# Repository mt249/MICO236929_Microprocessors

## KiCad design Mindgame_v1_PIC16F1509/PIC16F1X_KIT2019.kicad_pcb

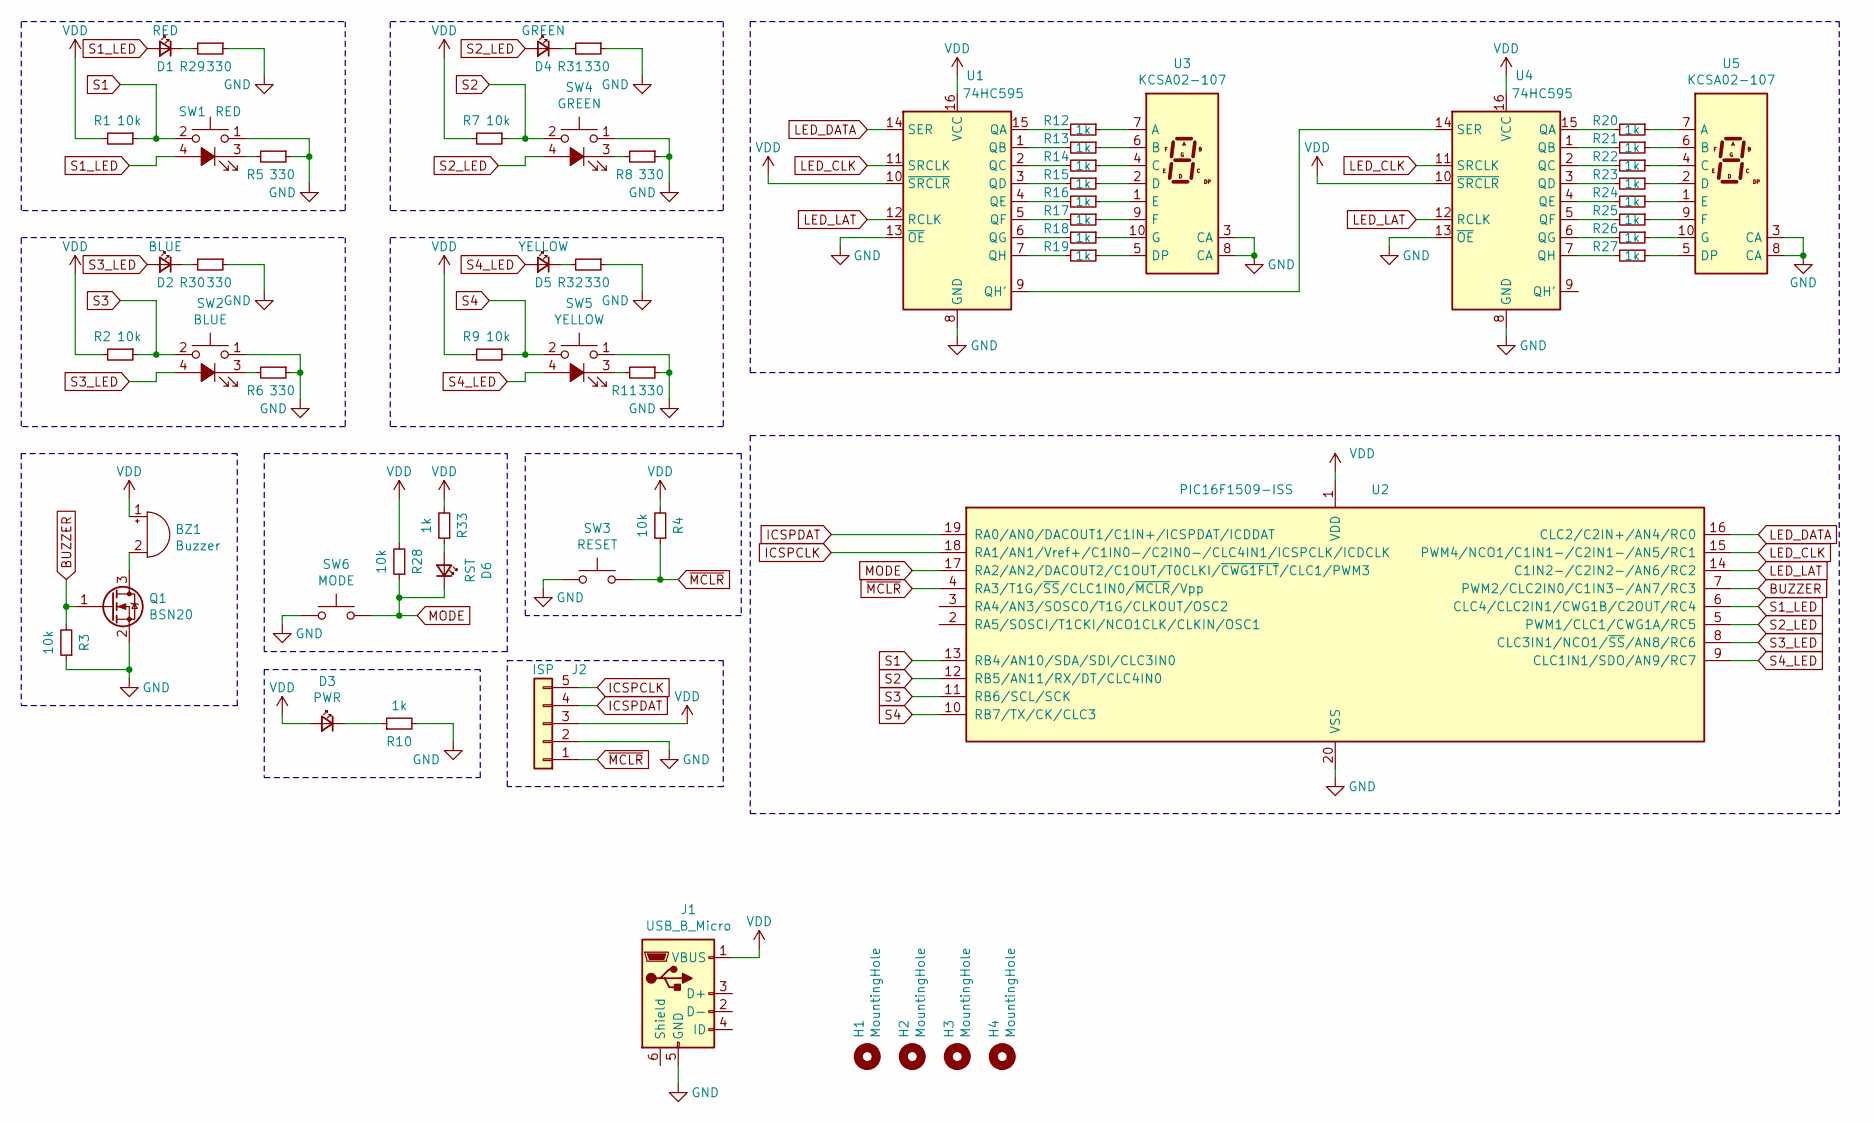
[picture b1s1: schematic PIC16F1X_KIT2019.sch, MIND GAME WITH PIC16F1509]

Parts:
BZ1: Buzzer; Buzzer_12x9.5RM7.6
D1: RED; LED_D8.0mm
D2: BLUE; LED_D8.0mm
D3: PWR; LED_0805_2012Metric_Pad1.15x1.40mm_HandSolder
D4: GREEN; LED_D8.0mm
D5: YELLOW; LED_D8.0mm
D6: RST; LED_0805_2012Metric_Pad1.15x1.40mm_HandSolder
H1, H2, H3, H4: MountingHole; MountingHole_2.7mm_M2.5_ISO7380_Pad
J1: USB_B_Micro; USB_Micro-B_GCT_USB3076-30-A
J2: ISP; PinHeader_1x05_P2.54mm_Horizontal
Q1: BSN20; SOT-23
R1, R2, R3, R4, R7, R9, R28: 10k; R_0603_1608Metric_Pad1.05x0.95mm_HandSolder
R5, R6, R8, R11, R29, R30, R31, R32: 330; R_0805_2012Metric_Pad1.15x1.40mm_HandSolder
R10, R12, R13, R14, R15, R16, R17, R18, R19, R20, R21, R22, R23, R24, R25, R26, R27, R33: 1k; R_0603_1608Metric_Pad1.05x0.95mm_HandSolder
SW1: RED; SW_PUSH-12mm
SW2: BLUE; SW_PUSH-12mm
SW3: RESET; SW_SPST_CK_RS282G05A3
SW4: GREEN; SW_PUSH-12mm
SW5: YELLOW; SW_PUSH-12mm
SW6: MODE; SW_SPST_CK_RS282G05A3
U1, U4: 74HC595; SOIC-16_3.9x9.9mm_P1.27mm
U2: PIC16F1509-ISS; SSOP-20_5.3x7.2mm_P0.65mm
U3, U5: KCSA02-107; 7SegmentLED_LTS6760_LTS6780

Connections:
BUZZER: Q1.1 (G), R3.2, U2.7 (PWM2/CLC2IN0/C1IN3-/AN7/RC3)
GND: J1.5 (GND), J2.2, Q1.2 (S), R3.1, R5.1, R6.1, R8.1, R10.2, R11.1, R29.1, R30.1, R31.1, R32.1, SW1.1, SW2.1, SW3.1, SW4.1, SW5.1, SW6.1, U1.8 (GND), U1.13 (~OE), U2.20 (VSS), U3.3 (CA), U3.8 (CA), U4.8 (GND), U4.13 (~OE), U5.3 (CA), U5.8 (CA); also elsewhere on the board
Hint: D6.1 (K), R28.1, SW6.2, U2.17 (RA2/AN2/DACOUT2/C1OUT/T0CLKI/~CWG1FLT~/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)
ICSPCLK: J2.5, U2.18 (RA1/AN1/Vref+/C1IN0-/C2IN0-/CLC4IN1/ICS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)
ICSPDAT: J2.4, U2.19 (RA0/AN0/DACOUT1/C1IN+/ICSPDAT/ICDDAT)
LED_CLK: U1.11 (SRCLK), U2.15 (PWM4/NCO1/C1IN1-/C2IN1-/AN5/RC1), U4.11 (SRCLK)
LED_DATA: U1.14 (SER), U2.16 (CLC2/C2IN+/AN4/RC0)
LED_LAT: U1.12 (RCLK), U2.14 (C1IN2-/C2IN2-/AN6/RC2), U4.12 (RCLK)
unnamed: BZ1.2 (+), Q1.3 (D)
unnamed 9: D1.1 (K), R29.2; also elsewhere on the board
unnamed 10: D2.1 (K), R30.2; also elsewhere on the board
unnamed: D3.1 (K), R10.1
unnamed 12: D4.1 (K), R31.2; also elsewhere on the board
unnamed 13: D5.1 (K), R32.2; also elsewhere on the board
unnamed: D6.2 (A), R33.1
unnamed: R5.2, SW1.3 (K)
unnamed: R6.2, SW2.3 (K)
unnamed: R8.2, SW4.3 (K)
unnamed: R11.2, SW5.3 (K)
unnamed: R12.1, U3.7 (A)
unnamed: R12.2, U1.15 (QA)
unnamed: R13.1, U3.6 (B)
unnamed: R13.2, U1.1 (QB)
unnamed: R14.1, U3.4 (C)
unnamed: R14.2, U1.2 (QC)
unnamed: R15.1, U3.2 (D)
unnamed: R15.2, U1.3 (QD)
unnamed: R16.1, U3.1 (E)
unnamed: R16.2, U1.4 (QE)
unnamed: R17.1, U3.9 (F)
unnamed: R17.2, U1.5 (QF)
unnamed: R18.1, U3.10 (G)
unnamed: R18.2, U1.6 (QG)
unnamed: R19.1, U3.5 (DP)
unnamed: R19.2, U1.7 (QH)
unnamed: R20.1, U5.7 (A)
unnamed: R20.2, U4.15 (QA)
unnamed: R21.1, U5.6 (B)
unnamed: R21.2, U4.1 (QB)
unnamed: R22.1, U5.4 (C)
unnamed: R22.2, U4.2 (QC)
unnamed: R23.1, U5.2 (D)
unnamed: R23.2, U4.3 (QD)
unnamed: R24.1, U5.1 (E)
unnamed: R24.2, U4.4 (QE)
unnamed: R25.1, U5.9 (F)
unnamed: R25.2, U4.5 (QF)
unnamed: R26.1, U5.10 (G)
unnamed: R26.2, U4.6 (QG)
unnamed: R27.1, U5.5 (DP)
unnamed: R27.2, U4.7 (QH)
unnamed: U1.9 (QH'), U4.14 (SER)
S1: R1.1, SW1.2, U2.13 (RB4/AN10/SDA/SDI/CLC3IN0)
S1_LED: D1.2 (A), SW1.4 (A), U2.6 (CLC4/CLC2IN1/CWG1B/C2OUT/RC4)
S2: R7.1, SW4.2, U2.12 (RB5/AN11/RX/DT/CLC4IN0)
S2_LED: D4.2 (A), SW4.4 (A), U2.5 (PWM1/CLC1/CWG1A/RC5)
S3: R2.1, SW2.2, U2.11 (RB6/SCL/SCK)
S3_LED: D2.2 (A), SW2.4 (A), U2.8 (CLC3IN1/NCO1/~SS~/AN8/RC6)
S4: R9.1, SW5.2, U2.10 (RB7/TX/CK/CLC3)
S4_LED: D5.2 (A), SW5.4 (A), U2.9 (CLC1IN1/SDO/AN9/RC7)
VDD: BZ1.1 (-), D3.2 (A), J1.1 (VBUS), J2.3, R1.2, R2.2, R4.2, R7.2, R9.2, R28.2, R33.2, U1.10 (~SRCLR), U1.16 (VCC), U2.1 (VDD), U4.10 (~SRCLR), U4.16 (VCC)
~MCLR~: J2.1, R4.1, SW3.2, U2.4 (RA3/T1G/~SS~/CLC1IN0/~MCLR~/Vpp)

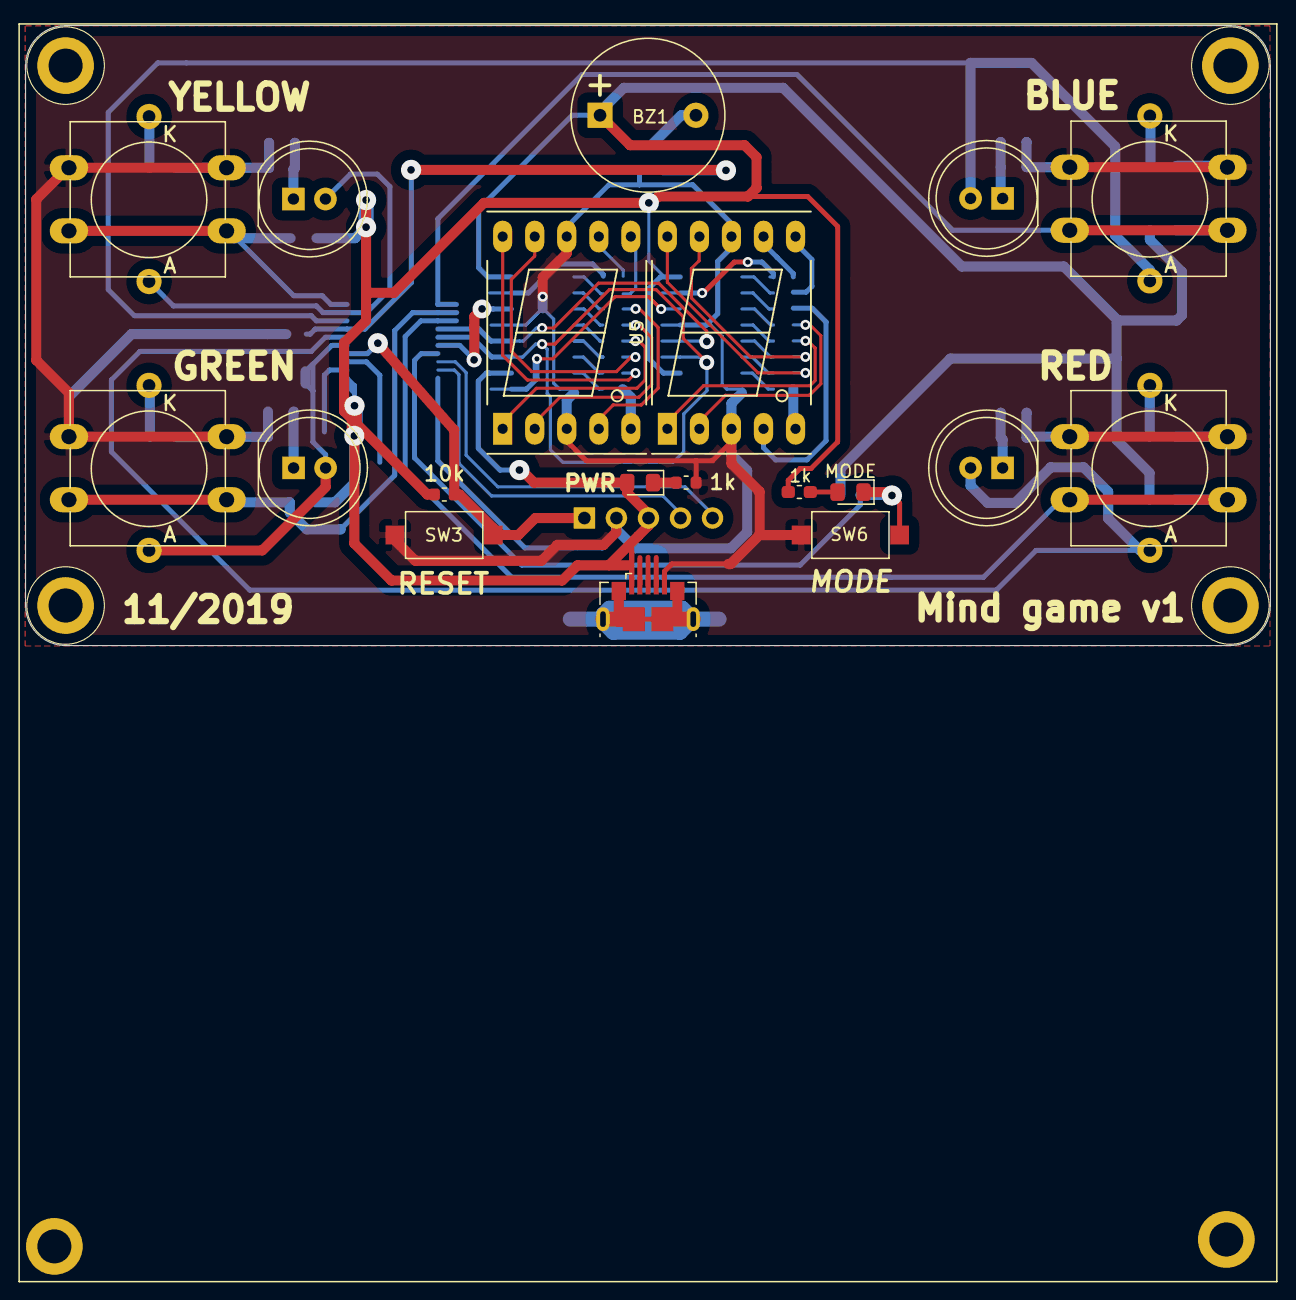
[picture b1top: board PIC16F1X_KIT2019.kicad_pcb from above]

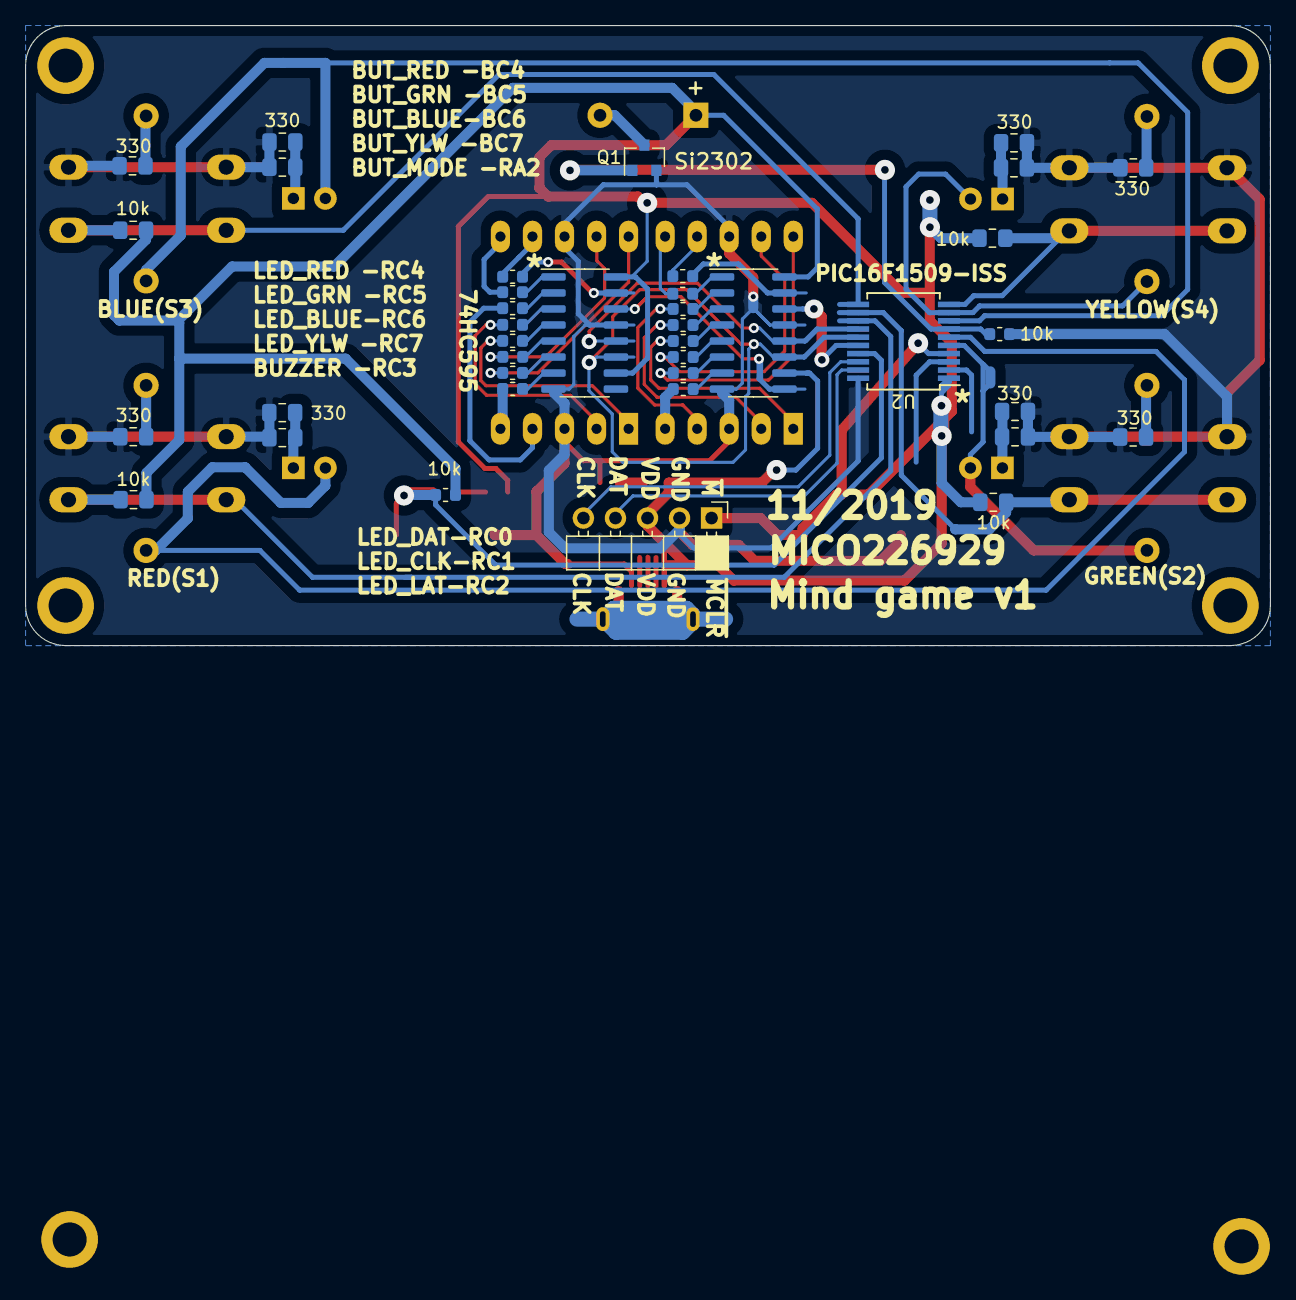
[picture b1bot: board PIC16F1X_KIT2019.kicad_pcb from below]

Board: 2 copper layers, 98.7 x 49.1 mm, 64 parts (39 on the bottom side), 62 nets.

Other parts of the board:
H1#2, H1#3: MountingHole; MountingHole_2.7mm_M2.5_ISO7380_Pad
R29#2, R30#2, R31#2, R32#2: 330; R_0805_2012Metric_Pad1.15x1.40mm_HandSolder

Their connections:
GND: R29#2.1, R30#2.1, R31#2.1, R32#2.1; also elsewhere on the board
unnamed 9: R29#2.2; also elsewhere on the board
unnamed 10: R30#2.2; also elsewhere on the board
unnamed 12: R31#2.2; also elsewhere on the board
unnamed 13: R32#2.2; also elsewhere on the board
